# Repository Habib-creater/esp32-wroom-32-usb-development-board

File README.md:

# ESP32-WROOM-32 USB Development Board

A complete 2-layer ESP32-WROOM-32E development board designed in KiCad, integrating USB-to-UART programming, protected USB power input, 3.3 V regulation, BOOT/RESET control, GPIO expansion, and protected I²C interfaces.

---

## Overview

This project presents the complete hardware design of a compact ESP32-WROOM-32E development board, including schematic capture, component selection, PCB layout, power distribution, interface protection, signal connectivity, design-rule verification, and manufacturing-data generation.

The design combines a Micro-USB interface, USB-to-UART bridge, regulated 3.3 V power architecture, ESP32 boot and reset circuitry, GPIO expansion headers, and protected I²C connectivity into a single 2-layer PCB.

The complete design package includes the KiCad schematic and PCB source files, bill of materials, manufacturing outputs, design documentation, PCB layout views, 3D board views, and verification records.

---

## Key Features

- ESP32-WROOM-32E based embedded hardware platform
- Micro-USB connectivity for power and USB communication
- CH340E USB-to-UART bridge powered from the +3.3 V rail
- AP2112K-3.3 low-dropout voltage regulator
- Protected USB power input with resettable fuse
- Dedicated USB ESD protection
- BOOT / GPIO0 programming control
- EN / RESET control
- GPIO expansion through dual 14-pin headers
- GPIO21 / GPIO22 dedicated to I²C SDA / SCL
- 4.7 kΩ I²C pull-up resistors
- AXGD10603NR low-capacitance ESD/TVS protection on I²C lines
- Local IC decoupling and bulk power filtering
- ESP32 antenna-region and RF keepout consideration
- 2-layer PCB layout
- Complete KiCad schematic and PCB source files
- Bill of Materials (BOM)
- Gerber and drill manufacturing outputs
- Electrical Rules Check (ERC) completed
- Design Rules Check (DRC) completed

---

## Project Specifications

| Parameter | Specification |
|---|---|
| MCU / Module | Espressif ESP32-WROOM-32E-H4 |
| USB Connector | Micro-USB, Molex 105017-0001 |
| USB-UART Bridge | CH340E |
| CH340E Supply | +3.3 V |
| Voltage Regulator | AP2112K-3.3 |
| USB ESD Protection | SP0503BAHT |
| I²C ESD Protection | 2 × AXGD10603NR |
| I²C SDA | GPIO21 |
| I²C SCL | GPIO22 |
| I²C Pull-ups | 4.7 kΩ to +3.3 V |
| Logic Voltage | 3.3 V |
| PCB Layers | 2 |
| PCB Thickness | 1.6 mm nominal |
| Board Dimensions | 51.75 mm × 31.00 mm |
| CAD Platform | KiCad 9.x |
| Design Verification | ERC + DRC completed |
| Hardware Status | PCB not yet fabricated |

---

## Functional Architecture

```mermaid
flowchart LR
    USB[Micro-USB] --> ESD[USB ESD Protection]
    ESD --> FUSE[500 mA Resettable Fuse]
    FUSE --> V5[+5 V Rail]

    V5 --> LDO[AP2112K-3.3]
    LDO --> V3[+3.3 V Rail]

    V3 --> ESP[ESP32-WROOM-32E]
    V3 --> UART[CH340E USB-UART]
    V3 --> I2C[I²C Pull-ups]

    UART <-->|UART0| ESP

    BOOT[BOOT / GPIO0] --> ESP
    RESET[EN / RESET] --> ESP

    I2C --> SDA[GPIO21 / SDA]
    I2C --> SCL[GPIO22 / SCL]

    SDA --> ESP
    SCL --> ESP

    ESP --> GPIO[GPIO Expansion Headers]
```

---

---

## Schematic

## Schematic

The complete electrical schematic is available as a PDF for detailed review.

[📄 View ESP32-WROOM-32 Schematic PDF](./archive/original/ESP32-WROOM-32-Schematic-original-export.pdf)

The PDF contains the complete electrical design, including:

- USB Micro-B input and power interface
- USB ESD protection
- Resettable USB input protection
- AP2112K-3.3 voltage regulation
- CH340E USB-to-UART interface
- ESP32-WROOM-32E module
- BOOT / GPIO0 control
- EN / RESET circuitry
- GPIO expansion headers
- I²C SDA / SCL interface
- I²C pull-up resistors
- I²C ESD/TVS protection
- Power decoupling and filtering
## PCB Layout

The PCB is a compact **51.75 mm × 31.00 mm, 2-layer design** with a nominal thickness of 1.6 mm.

### Layout View 1

### Layout View 2

The PCB layout was developed with consideration for:

- ESP32 antenna region and RF keepout
- USB interface routing
- Power distribution
- Ground return paths
- Local IC decoupling
- Component placement
- Manufacturing clearances
- Board-edge constraints
- Signal routing

---

## PCB Routing

The completed PCB routing is shown below.

The routing includes:

- USB D+ / D−
- USB-to-UART connections
- ESP32 UART connections
- I²C signals
- Power distribution
- GPIO connections
- Ground connections

---

## 3D Board Views

### Front View

### Back View

---

## Design Verification

The schematic and PCB were reviewed using KiCad's electrical and physical design verification tools.

### Electrical Rules Check (ERC)

ERC was completed to review:

- Power connectivity
- Pin electrical types
- Net connectivity
- Unconnected pins
- Driver conflicts
- Interface connections
- Electrical rule violations

Relevant ERC issues were reviewed and resolved as part of the schematic verification process.

### Design Rules Check (DRC)

PCB DRC was completed to review:

- Track clearances
- Pad clearances
- Via clearances
- Board-edge clearances
- Copper constraints
- Solder-mask constraints
- Connectivity
- Manufacturing-rule constraints

The resulting PCB layout was reviewed for unresolved critical DRC violations.

### Verification Summary

| Verification Item | Status |
|---|---|
| Schematic ERC | ✅ Completed |
| PCB DRC | ✅ Completed |
| Net Connectivity | ✅ Reviewed |
| Component Footprints | ✅ Reviewed |
| Board Dimensions | ✅ Verified |
| Manufacturing Outputs | ✅ Generated |

---

## Manufacturing Data

The repository includes the generated manufacturing data associated with the PCB design.

The manufacturing package contains:

- Gerber copper layers
- Solder-mask layers
- Silkscreen layers
- Paste layers
- Board outline
- Drill files

**[View Manufacturing Documentation](docs/MANUFACTURING.md)**

---

## Bill of Materials

The project includes a component-level Bill of Materials for the board.

**[View Bill of Materials](hardware/bom/ESP32-WROOM-32_BOM.csv)**

The BOM contains component references, values, footprints, and available part/manufacturer information.

---

## Repository Structure

```text
ESP32-WROOM-32-USB-Development-Board/
│
├── README.md
├── LICENSE
├── CHANGELOG.md
├── .gitignore
├── .gitattributes
│
├── ESP32-WROOM-32-Schematic-original-export.pdf
│
├── hardware/
│   ├── kicad/
│   │   ├── ESP32-WROOM-32.kicad_pro
│   │   ├── ESP32-WROOM-32.kicad_sch
│   │   └── ESP32-WROOM-32.kicad_pcb
│   │
│   ├── bom/
│   │   └── ESP32-WROOM-32_BOM.csv
│   │
│   └── fabrication/
│       └── gerbers/
│
├── docs/
│   ├── SCHEMATIC.md
│   ├── ARCHITECTURE.md
│   ├── PINOUT.md
│   ├── MANUFACTURING.md
│   ├── VALIDATION.md
│   │
│   └── images/
│       ├── 3d-front.png
│       ├── 3d-back.png
│       ├── 3d_2.png
│       ├── pcb-layout.png
│       ├── pcb-layout-alternate.png
│       └── pcb-routing.png
│
├── project/
│   ├── design-notes.md
│   ├── repository-audit.md
│   └── SHA256SUMS.md
│
└── archive/
    └── original/
```

---

## Design Documentation

| Document | Description |
|---|---|
| [Architecture](docs/ARCHITECTURE.md) | Functional and power architecture |
| [Schematic Documentation](docs/SCHEMATIC.md) | Schematic organization and design blocks |
| [Pinout](docs/PINOUT.md) | GPIO and interface mapping |
| [Manufacturing](docs/MANUFACTURING.md) | Manufacturing-data inventory |
| [Validation](docs/VALIDATION.md) | Design verification information |
| [Design Notes](project/design-notes.md) | Engineering design notes |
| [Repository Audit](project/repository-audit.md) | Project package scope and status |

---

## Current Design Status

**Status: PCB design package completed**

The schematic, PCB layout, component selection, BOM, manufacturing outputs, and CAD-level design verification have been completed.

The PCB has **not yet been fabricated or hardware-validated**.

The repository therefore documents the CAD design and generated engineering files without claiming measured electrical, RF, thermal, assembly, or production results.

---

## Tools and Technologies

- KiCad 9.x
- Schematic Capture
- PCB Layout
- Electrical Rules Check (ERC)
- Design Rules Check (DRC)
- Gerber Generation
- Drill File Generation
- Bill of Materials Generation
- 3D PCB Visualization
- USB-UART Interface Design
- Power Supply Design
- ESD Protection
- I²C Interface Design

---

## License

This hardware design is released under the **CERN Open Hardware Licence Version 2 – Strongly Reciprocal (CERN-OHL-S-2.0)**.

See the [`LICENSE`](LICENSE) file for the complete licence terms.

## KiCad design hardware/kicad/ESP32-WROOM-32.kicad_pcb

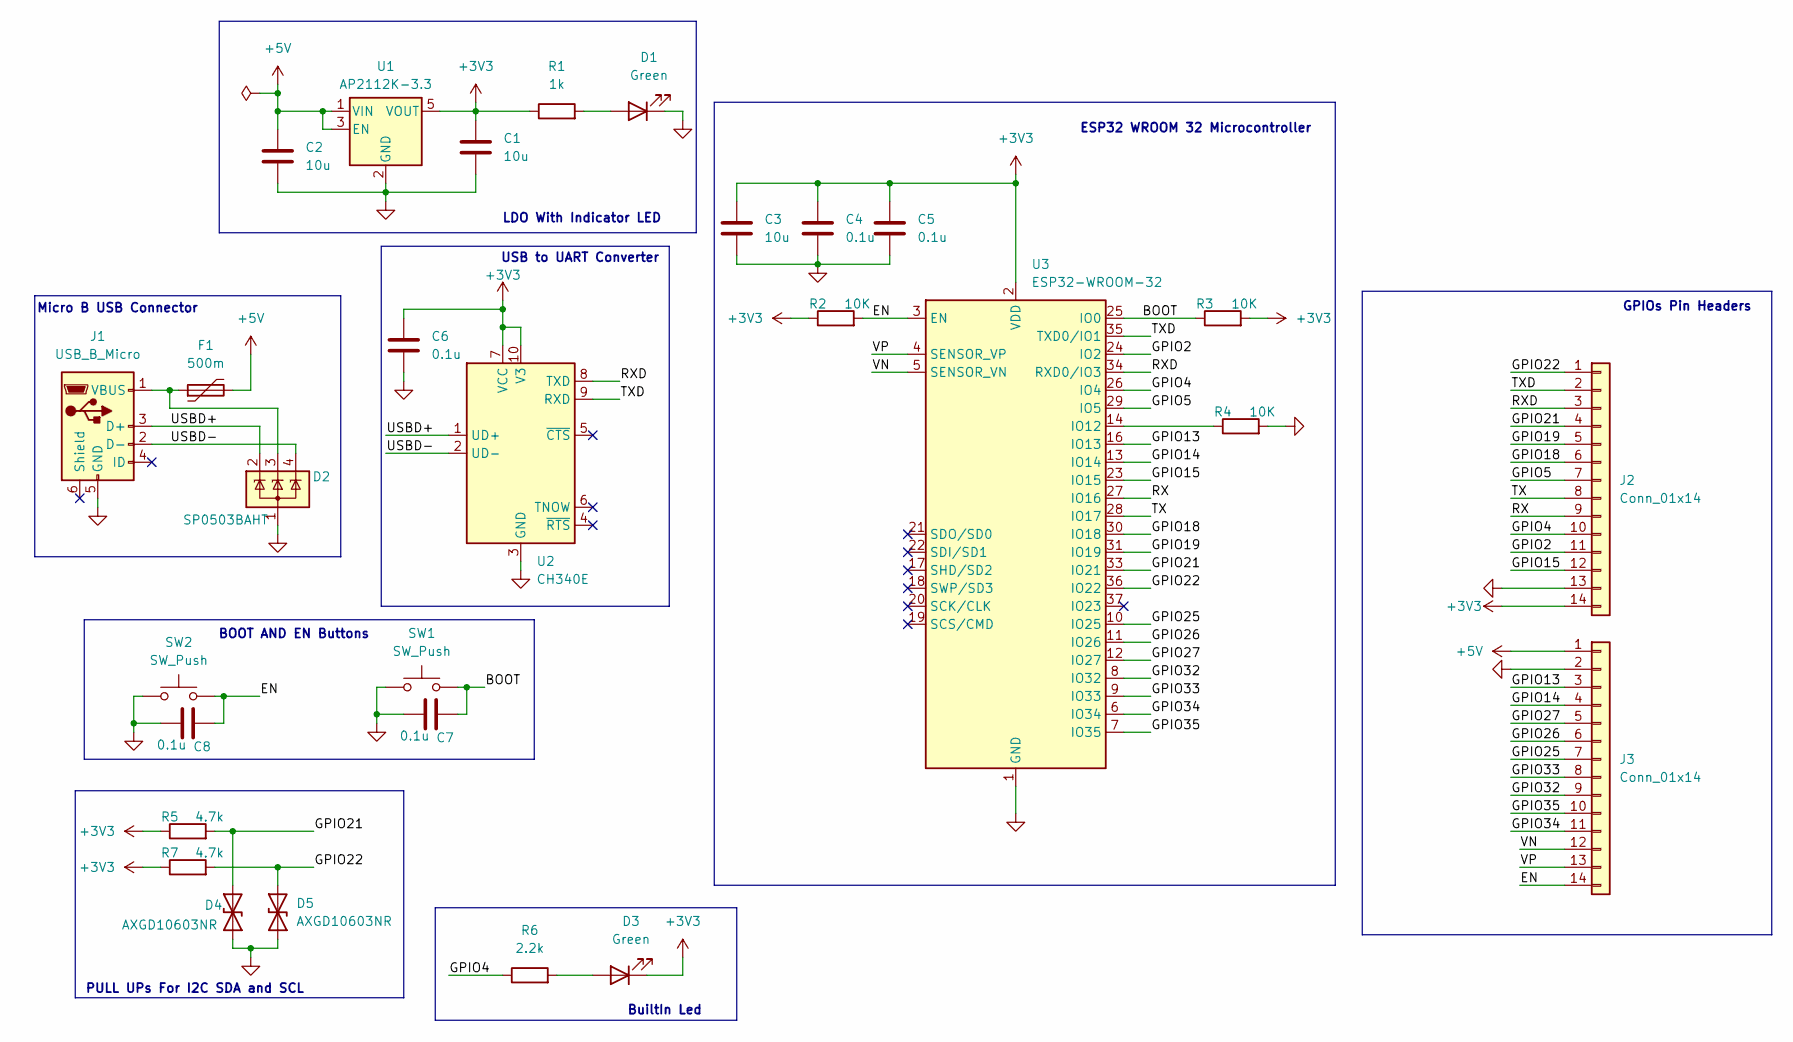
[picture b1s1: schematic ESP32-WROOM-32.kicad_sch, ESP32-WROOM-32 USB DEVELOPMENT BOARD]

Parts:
C1, C2, C3: 10u; C_0603_1608Metric_Pad1.08x0.95mm_HandSolder
C4, C5, C6, C7, C8: 0.1u; C_0603_1608Metric_Pad1.08x0.95mm_HandSolder
D1, D3: Green; LED_0603_1608Metric_Pad1.05x0.95mm_HandSolder
D2: SP0503BAHT; SOT-23-5
D4, D5: AXGD10603NR; D_0603_1608Metric_Pad1.05x0.95mm_HandSolder
F1: 500m; Fuse_1206_3216Metric
J1: USB_B_Micro; USB_Micro-B_Molex-105017-0001
J2, J3: Conn_01x14; PinHeader_1x14_P2.54mm_Vertical
R1: 1k; R_0603_1608Metric_Pad0.98x0.95mm_HandSolder
R2, R3, R4: 10K; R_0603_1608Metric_Pad0.98x0.95mm_HandSolder
R5, R7: 4.7k; R_0603_1608Metric_Pad0.98x0.95mm_HandSolder
R6: 2.2k; R_0603_1608Metric_Pad0.98x0.95mm_HandSolder
SW1, SW2: SW_Push; SW_SPST_B3U-1000P
U1: AP2112K-3.3; SOT-23-5
U2: CH340E; MSOP-10_3x3mm_P0.5mm
U3: ESP32-WROOM-32

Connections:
+3V3: C1.1, C3.1, C4.1, C5.1, C6.1, D3.1 (K), J2.14, R1.1, R2.1, R3.2, R5.1, R7.1, U1.5 (VOUT), U2.7 (VCC), U2.10 (V3), U3.2 (VDD)
+5V: C2.1, F1.2, J3.1, U1.1 (VIN), U1.3 (EN)
/BOOT: C7.1, R3.1, SW1.2, U3.25 (IO0)
/EN: C8.1, J3.14, R2.2, SW2.2, U3.3 (EN)
/GPIO2: J2.11, U3.24 (IO2)
/GPIO4: J2.10, R6.1, U3.26 (IO4)
/GPIO5: J2.7, U3.29 (IO5)
/GPIO13: J3.3, U3.16 (IO13)
/GPIO14: J3.4, U3.13 (IO14)
/GPIO15: J2.12, U3.23 (IO15)
/GPIO18: J2.6, U3.30 (IO18)
/GPIO19: J2.5, U3.31 (IO19)
/GPIO21: D4.2 (A2), J2.4, R5.2, U3.33 (IO21)
/GPIO22: D5.2 (A2), J2.1, R7.2, U3.36 (IO22)
/GPIO25: J3.7, U3.10 (IO25)
/GPIO26: J3.6, U3.11 (IO26)
/GPIO27: J3.5, U3.12 (IO27)
/GPIO32: J3.9, U3.8 (IO32)
/GPIO33: J3.8, U3.9 (IO33)
/GPIO34: J3.11, U3.6 (IO34)
/GPIO35: J3.10, U3.7 (IO35)
/RX: J2.9, U3.27 (IO16)
/RXD: J2.3, U2.8 (TXD), U3.34 (RXD0/IO3)
/TX: J2.8, U3.28 (IO17)
/TXD: J2.2, U2.9 (RXD), U3.35 (TXD0/IO1)
/USBD+: D2.2 (K), J1.3 (D+), U2.1 (UD+)
/USBD-: D2.4 (K), J1.2 (D-), U2.2 (UD-)
/VN: J3.12, U3.5 (SENSOR_VN)
/VP: J3.13, U3.4 (SENSOR_VP)
GND: C1.2, C2.2, C3.2, C4.2, C5.2, C6.2, C7.2, C8.2, D1.1 (K), D2.1 (A), D4.1 (A1), D5.1 (A1), J1.5 (GND), J2.13, J3.2, R4.2, SW1.1, SW2.1, U1.2 (GND), U2.3 (GND), U3.1 (GND), U3.15 (GND), U3.38 (GND), U3.39 (GND)
unnamed: D1.2 (A), R1.2
unnamed: D3.2 (A), R6.2
unnamed: D2.3 (K), F1.1, J1.1 (VBUS)
unnamed: R4.1, U3.14 (IO12)

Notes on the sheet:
PULL UPs For I2C SDA and SCL
Micro B USB Connector
BOOT AND EN Buttons
GPIOs Pin Headers
BuiltIn Led
LDO With Indicator LED
ESP32 WROOM 32 Microcontroller
USB to UART Converter

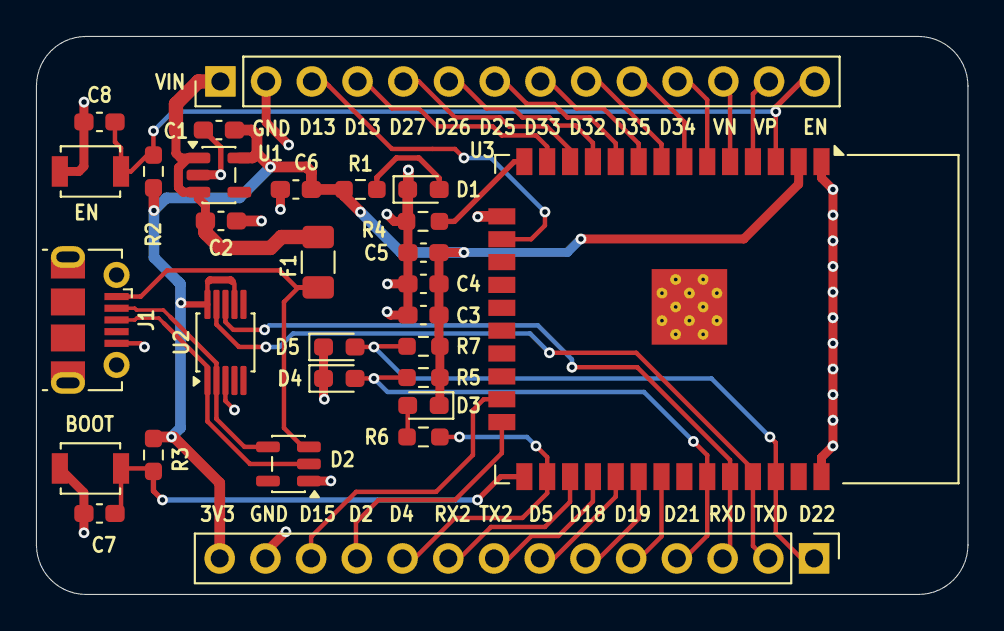
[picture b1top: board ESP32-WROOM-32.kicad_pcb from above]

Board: 2 copper layers, 51.8 x 31.0 mm, 29 parts (0 on the bottom side), 34 nets.

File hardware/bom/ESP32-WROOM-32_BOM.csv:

Reference,Qty,Value,Footprint,Manufacturer,Manufactuerr Part No,Suppier Name,Supplier Link,Supplier Part No 
"C1,C2,C3",3,10u,Capacitor_SMD:C_0603_1608Metric_Pad1.08x0.95mm_HandSolder,YAGEO,CC0603MRX5R7BB106,DigiKey,https://www.digikey.com/en/products/detail/yageo/CC0603MRX5R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,311-1822-1-ND
"C4,C5,C6,C7,C8",5,0.1u,Capacitor_SMD:C_0603_1608Metric_Pad1.08x0.95mm_HandSolder,YAGEO,CC0603KRX7R7BB104,DigiKey,https://www.digikey.com/en/products/detail/yageo/CC0603KRX7R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,311-1088-1-ND
"D1,D3",2,Green,LED_SMD:LED_0603_1608Metric_Pad1.05x0.95mm_HandSolder,Vishay Semiconductor Opto Division,VLMG1300-GS08,DigiKey,https://www.digikey.com/en/products/detail/vishay-semiconduc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,VLMG1300-GS08CT-ND
D2,1,SP0503BAHT,Package_TO_SOT_SMD:SOT-23-5,Littelfuse Inc.,SP0503BAHT,DigiKey,https://www.digikey.com/en/products/detail/littelfuse-inc/SP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,SP0503BAHT-ND
"D4,D5",2,ESD/TVS Protection,Diode_SMD:D_0603_1608Metric_Pad1.05x0.95mm_HandSolder,Littelfuse Inc.,AXGD10603NR,DigiKey,https://www.digikey.com/en/products/detail/littelfuse-inc/AX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,F10020CT-ND
F1,1,500m,Fuse:Fuse_1206_3216Metric,Meritek,MPTS1206L050,DigiKey,https://www.digikey.com/en/products/detail/meritek/MPTS1206L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,2997-MPTS1206L050TR-ND
J1,1,USB_B_Micro,Connector_USB:USB_Micro-B_Molex-105017-0001,Molex,1050170001,DigiKey,https://www.digikey.com/en/products/detail/molex/1050170001/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,WM1399CT-ND
"J2,J3",2,Conn_01x14,Connector_PinHeader_2.54mm:PinHeader_1x14_P2.54mm_Vertical,Same Sky (Formerly CUI Devices),SSK01-MPH-254-A14,DigiKey,https://www.digikey.com/en/products/detail/same-sky-formerly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,2223-SSK01-MPH-254-A14-ND
R1,1,1k,Resistor_SMD:R_0603_1608Metric_Pad0.98x0.95mm_HandSolder,YAGEO,RC0603FR-071KL,DigiKey,https://www.digikey.com/en/products/detail/yageo/RC0603FR-07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,311-1.00KHRCT-ND
"R2,R3,R4",3,10K,Resistor_SMD:R_0603_1608Metric_Pad0.98x0.95mm_HandSolder,YAGEO,RC0603FR-0710KL,DigiKey,https://www.digikey.com/en/products/detail/yageo/RC0603FR-07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,311-10.0KHRCT-ND
"R5,R7",2,4.7k,Resistor_SMD:R_0603_1608Metric_Pad0.98x0.95mm_HandSolder,YAGEO,RC0603FR-074K7L,DigiKey,https://www.digikey.com/en/products/detail/yageo/RC0603FR-07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,311-4.70KHRCT-ND
R6,1,2.2k,Resistor_SMD:R_0603_1608Metric_Pad0.98x0.95mm_HandSolder,YAGEO,RC0603FR-072K2L,DigiKey,https://www.digikey.com/en/products/detail/yageo/RC0603FR-07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,311-2.20KHRCT-ND
"SW1,SW2",2,SW_Push,Button_Switch_SMD:SW_SPST_B3U-1000P,Aratas (Formerly Omron Components),B3U-1000P,DigiKey,https://www.digikey.com/en/products/detail/aratas-formerly-o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,SW1020CT-ND
U1,1,AP2112K-3.3,Package_TO_SOT_SMD:SOT-23-5,Diodes Incorporated,AP2112K-3.3TRG1,DigiKey,https://www.digikey.com/en/products/detail/diodes-incorporat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,AP2112K-3.3TRG1DICT-ND
U2,1,CH340E,Package_SO:MSOP-10_3x3mm_P0.5mm,SparkFun Electronics,16278,DigiKey,https://www.digikey.com/en/products/detail/sparkfun-electron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,1568-16278-ND
U3,1,ESP32-WROOM-32,RF_Module:ESP32-WROOM-32,Espressif Systems,ESP32-WROOM-32E-H4,DigiKey,https://www.digikey.com/en/products/detail/espressif-systems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,1965-ESP32-WROOM-32E-H4CT-ND
